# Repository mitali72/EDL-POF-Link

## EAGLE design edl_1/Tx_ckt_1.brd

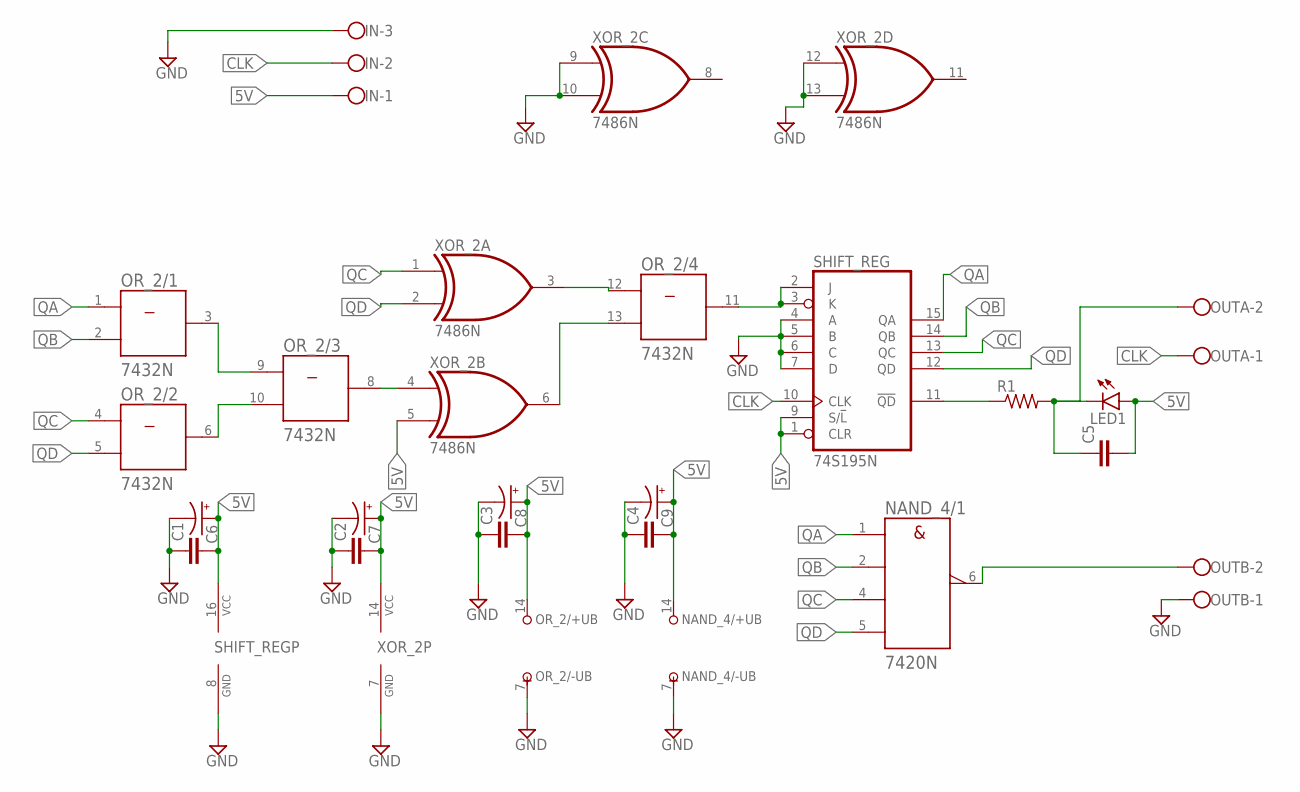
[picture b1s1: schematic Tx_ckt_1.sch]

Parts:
C1, C2, C3, C4, C5: C-EU050-025X075; C050-025X075
C6, C7, C8, C9: CPOL-USE2.5-7; E2,5-7
IN: W237-103
LED1: LED5MM
NAND_4: 7420N; DIL14
OR_2: 7432N; DIL14
OUTA: W237-102
OUTB: W237-102
R1: R-US_0207/10; 0207/10
SHIFT_REG: 74S195N; DIL16
XOR_2: 7486N; DIL14

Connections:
5V: C1.2, C2.2, C3.2, C4.2, C5.2, C6.+, C7.+, C8.+, C9.+, IN.1, LED1.A, NAND_4.14 (+UB), OR_2.14 (+UB), SHIFT_REG.1 (CLR), SHIFT_REG.9 (S/!L), SHIFT_REG.16 (VCC), XOR_2.5 (I1), XOR_2.14 (VCC)
CLK: IN.2, OUTA.1, SHIFT_REG.10 (CLK)
GND: C1.1, C2.1, C3.1, C4.1, C6.-, C7.-, C8.-, C9.-, IN.3, NAND_4.7 (-UB), OR_2.7 (-UB), OUTB.1, SHIFT_REG.4 (A), SHIFT_REG.5 (B), SHIFT_REG.6 (C), SHIFT_REG.7 (D), SHIFT_REG.8 (GND), XOR_2.7 (GND), XOR_2.9 (I0), XOR_2.10 (I1), XOR_2.12 (I0), XOR_2.13 (I1)
unnamed: OR_2.11 (Y), SHIFT_REG.2 (J), SHIFT_REG.3 (K)
unnamed: OR_2.12 (A), XOR_2.3 (O)
unnamed: OR_2.13 (B), XOR_2.6 (O)
unnamed: R1.1, SHIFT_REG.11 (!QD)
unnamed: C5.1, LED1.K (C), OUTA.2, R1.2
unnamed: NAND_4.6 (Y), OUTB.2
unnamed: OR_2.3 (Y), OR_2.9 (A)
unnamed: OR_2.6 (Y), OR_2.10 (B)
unnamed: OR_2.8 (Y), XOR_2.4 (I0)
QA: NAND_4.1 (A), OR_2.1 (A), SHIFT_REG.15 (QA)
QB: NAND_4.2 (B), OR_2.2 (B), SHIFT_REG.14 (QB)
QC: NAND_4.4 (C), OR_2.4 (A), SHIFT_REG.13 (QC), XOR_2.1 (I0)
QD: NAND_4.5 (D), OR_2.5 (B), SHIFT_REG.12 (QD), XOR_2.2 (I1)

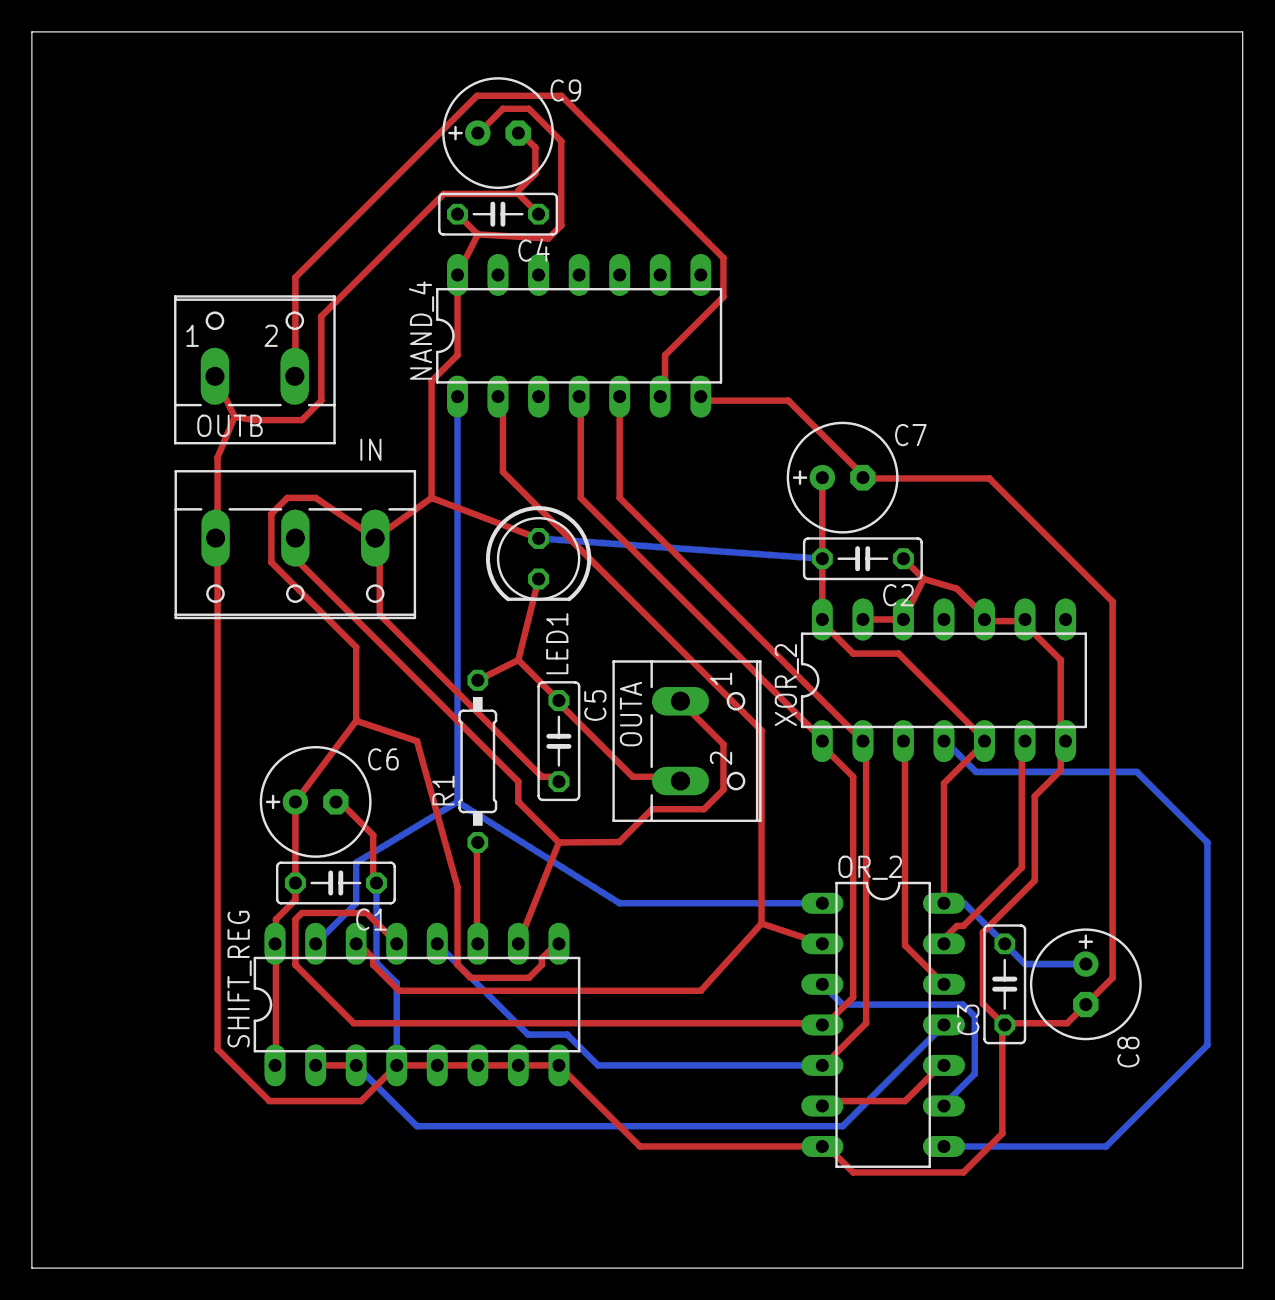
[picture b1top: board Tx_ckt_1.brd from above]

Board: 2 copper layers, 75.9 x 77.5 mm, 18 parts (0 on the bottom side), 16 nets.

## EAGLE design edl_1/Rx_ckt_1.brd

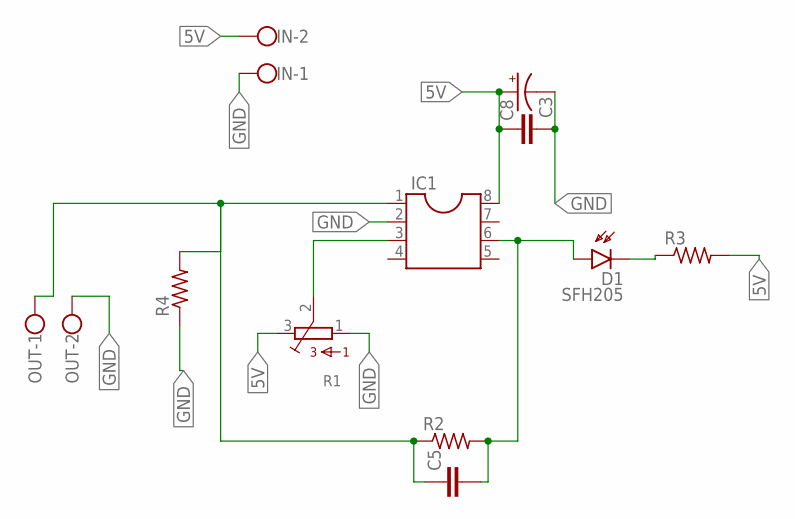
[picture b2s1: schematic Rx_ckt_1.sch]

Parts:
C3, C5: C-EU050-025X075; C050-025X075
C8: CPOL-USE2.5-7; E2,5-7
D1: SFH205
IC1: DIL8; DIL08
IN: W237-102
OUT: W237-102
R1: 3386-F; 3386F
R2, R3, R4: R-US_0207/10; 0207/10

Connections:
5V: C3.2, C8.+, IC1.8, IN.2, R1.3, R3.2
GND: C3.1, C8.-, IC1.2, IN.1, OUT.2, R1.1, R4.1
unnamed: IC1.3, R1.2
unnamed: C5.1, IC1.1, OUT.1, R2.1, R4.2
unnamed: C5.2, D1.A, IC1.6, R2.2
unnamed: D1.K (C), R3.1

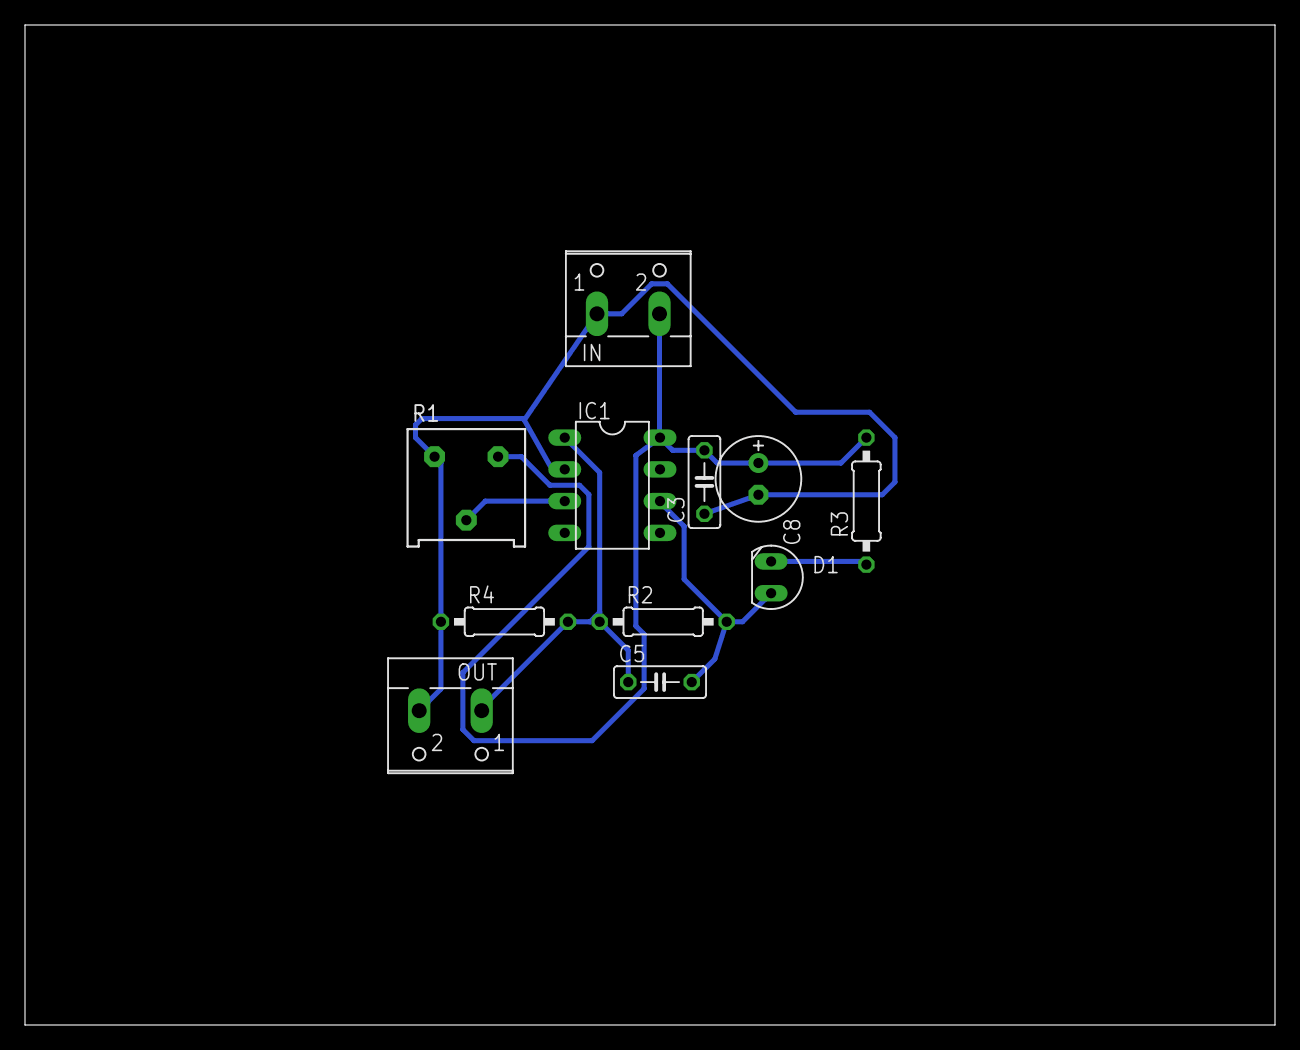
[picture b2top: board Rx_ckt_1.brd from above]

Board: 2 copper layers, 100.0 x 80.0 mm, 11 parts (0 on the bottom side), 6 nets.
